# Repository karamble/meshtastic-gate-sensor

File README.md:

# Meshtastic Gate & Door Sensor

Carrier board + firmware that bridges a cheap 433 MHz wireless door sensor onto a private Meshtastic LoRa mesh. A trigger on the door raises an event on the mesh — no WiFi, no cloud, no gateway.

## Architecture

```
KERUI D026 (433 MHz) → RXB6 Receiver → Arduino Nano → UART → Heltec LoRa32 V3 → LoRa mesh
```

The 433 MHz sensor broadcasts a fixed code on every open/close event. An Arduino Nano decodes the code with `rc-switch` on D2 (INT0) and forwards a short text line over SoftwareSerial D3 → voltage divider → Heltec GPIO47. The Heltec runs stock Meshtastic with the serial module in `TEXTMSG` mode at 9600 baud and relays each line into the mesh. A 10 s debounce collapses the KERUI retransmit burst into one mesh event per physical opening.

Firmware emits `Gate: TRIGGERED` on every event and `GATE NODE: Online` every 5 minutes as a heartbeat. KERUI D026 sends the same code on open and close, so `CODE_CLOSED` is disabled by default — one code per event is all you get.

Powered by a Waveshare Solar Power Manager D with 2× 18650 batteries and a 6 V 2 W solar panel. Total draw ≈ 105 mA.

## Carrier PCB v2.3

Custom 75×66 mm 2-layer board with:

- Heltec LoRa32 V3 socket (2×18 pins)
- Arduino Nano socket (2×15 pins, 15.24 mm row spacing)
- RXB6 433 MHz receiver (8-pin SIP, direct solder)
- Logic level divider 2.2k / 3.3k (5V → 3.0V on GPIO47)
- Hardening: 10k DE pull-up, 100nF bypass, 100µF bulk
- GND copper pour on both layers
- 0 DRC violations, 34 netlist self-checks pass

Generated programmatically by `pcb/gate_sensor_pcb_v2.py` and validated with KiCad 10.

## Build

Requires Docker (for KiCad CLI) and PlatformIO.

```bash
make help            # show all targets

# PCB
make drc             # design rule check
make fab             # export Gerbers + drill for JLCPCB

# Firmware
make build           # compile
make upload          # flash the Nano
make monitor         # 115200 USB serial monitor
make learn-sensor    # discover a new 433 MHz sensor's code

# Heltec Meshtastic flash & configure (stock firmware)
./scripts/flash-heltec-meshtastic.sh           # defaults (auto-detect, EU_868)
./scripts/flash-heltec-meshtastic.sh --help
```

The flash script downloads the latest stock Meshtastic release, flashes the Heltec V3, applies the gate-sensor config (GPIO47 RX at 9600 baud, TEXTMSG mode, owner name `GateSensor`/`GATE`, GPS disabled, Bluetooth disabled) and verifies every setting before closing.

## Learning a new sensor

If you're using a different 433 MHz sensor than the KERUI D026, discover its code with:

```bash
make learn-sensor
```

Trigger the sensor a few times and watch for repeating `RF unknown: <decimal>` lines. Copy the decimal into `CODE_OPEN` in `firmware/include/config.h`, re-run `make upload`, and the sensor will fire `Gate: TRIGGERED` on the mesh. See [docs/learn-sensor.md](docs/learn-sensor.md) for details.

## Project Structure

```
├── Makefile                      # build targets (KiCad Docker + PlatformIO)
├── pcb/
│   ├── gate_sensor_pcb_v2.py     # PCB generator script
│   ├── gate_sensor_v2.kicad_pcb  # generated board
│   ├── test_netlist.py           # 34-check PCB self-test
│   ├── generate_assembly.py      # 3D assembly view generator
│   └── logo_silk.json            # raccoon logo silkscreen data
├── firmware/
│   ├── platformio.ini            # PlatformIO config (board=nanoatmega328new)
│   ├── src/main.cpp              # bridge firmware
│   └── include/config.h          # sensor codes, pin defs, timing
├── scripts/
│   └── flash-heltec-meshtastic.sh  # Heltec flash + config
├── docs/
│   ├── schematic.md              # schematic + netlist
│   ├── pcb.md                    # PCB design documentation
│   ├── firmware.md               # firmware documentation
│   ├── assembly.md               # assembly and setup guide
│   ├── learn-sensor.md           # discovering a new 433 MHz sensor code
│   ├── bom.md                    # bill of materials
│   └── ordering.md               # JLCPCB ordering guide
└── pin-outs/                     # component pinout reference images
```

## BOM

~$52 total for one complete sensor node. See [docs/bom.md](docs/bom.md) for the full bill of materials.

## License

ISC — see [LICENSE](LICENSE).

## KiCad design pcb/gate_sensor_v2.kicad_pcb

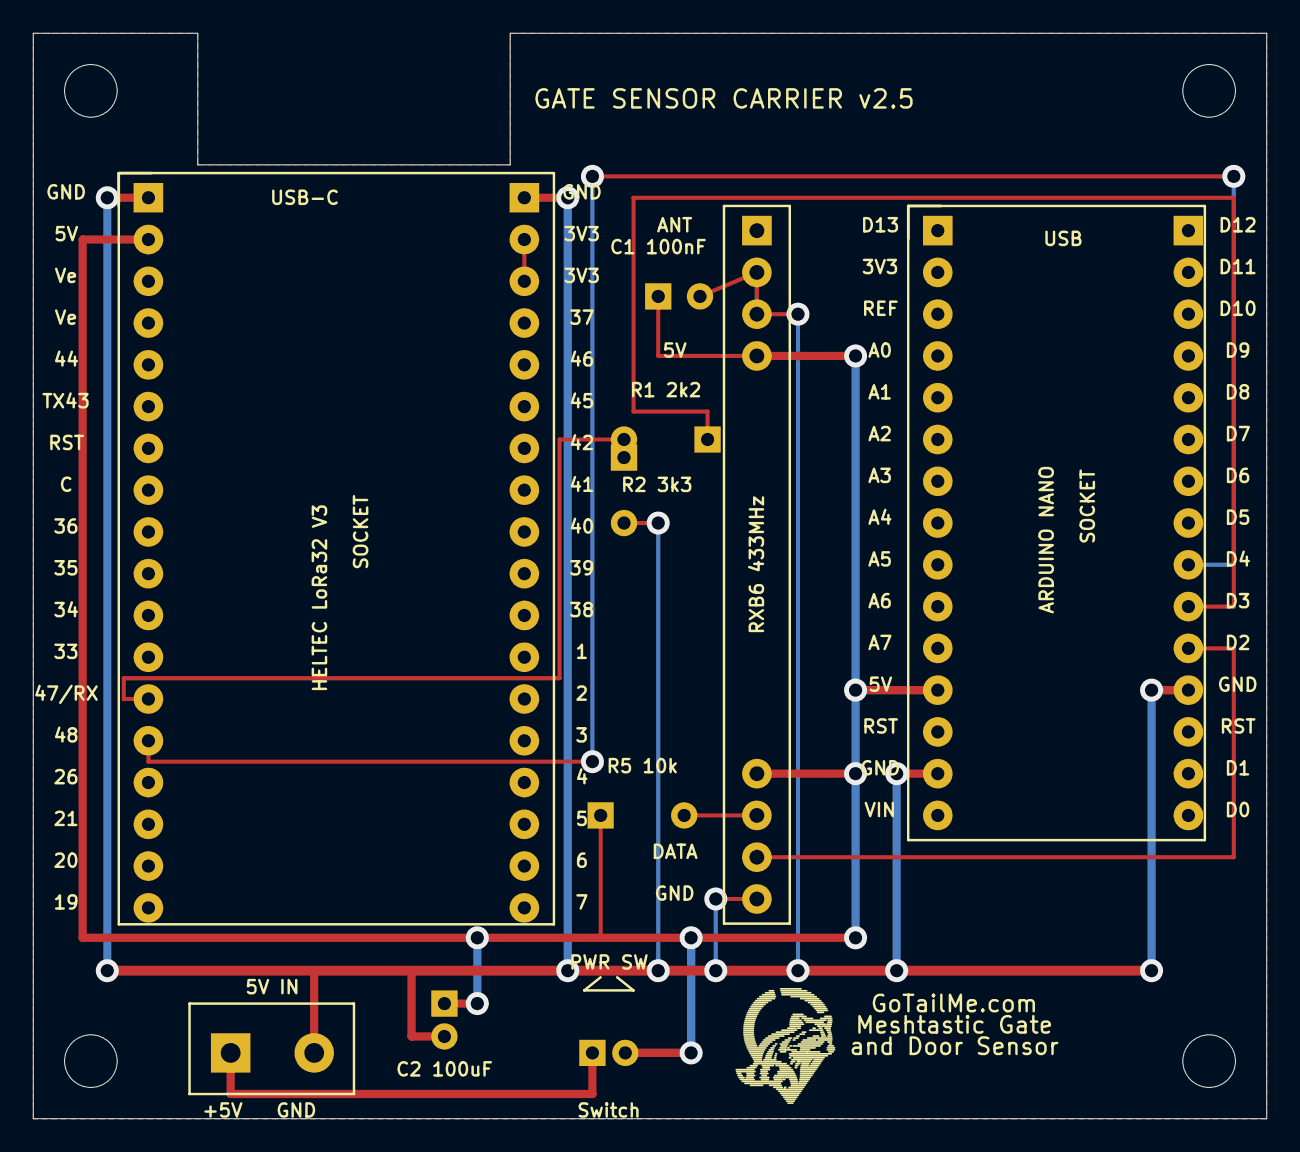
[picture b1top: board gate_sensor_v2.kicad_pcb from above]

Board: 2 copper layers, 75.0 x 66.0 mm, 14 parts (0 on the bottom side), 9 nets.

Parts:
C1: 100nF; C1
C2: 100uF; C2
J2: PWR_IN_ScrewTerm; J2
J4: PWR_SW_JST_PH_2pin; J4
MH: M3_MountHole; MH
MH#2, MH#3, MH#4: M3_MountHole; MH
R1: 2.2k; R1
R2: 3.3k; R2
R5: 10k_PU; R5
U1: Arduino_Nano_Socket; U1
U2: RXB6_433MHz_DirectSolder; U2
U3: Heltec_LoRa32_V3; U3

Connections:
3V3: U3.R2, U3.R3
5V: C1.1, C2.1, J4.2, R5.1, U1.L12, U2.4, U2.5, U3.L2
5V_IN: J2.1, J4.1
D2: U1.R11, U2.7
D3: R1.1, U1.R10
DE: R5.2, U2.6
GND: C1.2, C2.2, J2.2, R2.2, U1.L14, U1.R12, U2.2, U2.3, U2.8, U3.L1, U3.R1
HELTEC_RX: R1.2, R2.1, U3.L13
HELTEC_TX: U1.R9, U3.L14

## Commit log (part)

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2026-04-04 Initial commit — Gate Sensor Carrier PCB v2.2
    Meshtastic gate sensor carrier board (75x66mm, 2-layer) for
    Heltec LoRa32 V3 + Arduino Nano + RXB6 433MHz receiver.
    PCB: KiCad 10, generated by gate_sensor_pcb_v2.py, 0 DRC violations.
    Firmware: PlatformIO skeleton for ATmega328P bridge (RCSwitch + SoftwareSerial).
    Docs: schematic, BOM, assembly guide.
2026-04-04 Fix stale D4/GPIO44 references from pre-review pin changes
    Rename D4_NET→D2_NET and D4_RXB_X→D2_RXB_X to match actual wiring
    (RXB6 DATA connects to Nano D2/INT0, not D4). Fix silkscreen text
    from GPIO44 to GPIO47 for Heltec serial RX pin.
2026-04-04 PCB v2.3: remove battery monitoring, add 3D assembly view
    The Waveshare Solar Power Manager D handles battery internally —
    no BAT pin is accessible for voltage monitoring from the carrier PCB.
    PCB changes:
    - Remove R3, R4 (battery voltage divider) and J3 (battery connector)
    - Simplify V5 bus to straight run (no R4 notch)
    - Move R1/R2 right 2mm, restoring Heltec pins 40-42 to silkscreen
2026-04-05 Fix remaining stale D4 references in docs and comments
    The RF DATA net was renamed from D4 to D2 when the pin changed,
    but five documentation/comment locations still referenced D4.
2026-04-05 Add JLCPCB ordering guide
    Step-by-step guide for ordering PCBs from JLCPCB: Gerber export,
    order form settings, and recommended options for the 2-layer board.
2026-04-05 Fix Arduino Nano left/right pin swap and digital pin order
    The Nano socket had analog/power pins on the RIGHT and digital pins
    on the LEFT — reversed from the real board. Digital pin order was also
    inverted (D1 at USB end instead of D12). Verified against 4 reference
    pinout images.
    - Swap NL/NR arrays: LEFT=analog/power, RIGHT=digital (descending)
    - Re-route D3 (R10→R1) all-F.Cu via top of board
2026-04-05 Fix D0/D1 label order on Nano right column
    CH340 Nano pinout images (3 of 4 references) show D1 above D0 at the
    bottom of the digital pin column. Swap silkscreen labels to match.
    No routing impact — neither pin has a net connected.
2026-04-05 Adjust silkscreen labels: center socket names, add USB label to Nano
    - Move Heltec/Nano/RXB6 socket labels up for better vertical centering
    - Add "USB" label at top of Arduino Nano socket frame
    - Center R1 2k2 label above resistor body
2026-04-05 Add Heltec Meshtastic flash script for gate sensor node
    Automates flash + configure workflow for Heltec V3 as gate sensor:
    - BAUD_9600 (matches Nano SoftwareSerial)
    - serial.rxd=47 (GPIO47, avoids CP2102 conflict)
    - serial.txd=0 (one-way UART, Nano does not receive)
    - Stock Meshtastic firmware (no custom build required)
    - Includes config verification step
2026-04-05 Add PCB netlist verification test (34 checks)
    Validates net pad membership, forbidden connections, firmware pin
    mapping, Nano pin order (L/R swap regression), voltage divider
    correctness, and trace connectivity by parsing the generated KiCad
    PCB file. Run with: make test-netlist
2026-04-05 Update JLCPCB ordering guide with all form options
    Cover every high-spec and advanced option in the order form:
    via plating, min via size, blind slots, UL marking, 4-wire Kelvin
    test, appearance quality, silkscreen technology, package box,
    inspection report, and PCB remark fields.
2026-04-16 Calibrate Nano firmware to KERUI D026 sensor
    - CODE_OPEN=150910 — decimal value learned from a real KERUI D026 via
    rc-switch.
    - CODE_CLOSED disabled: the sensor emits the same code on open and
    close, so no distinct close event is decodable. Emit "TRIGGERED"
    rather than "OPEN" to match that reality.
    - DEBOUNCE_MS raised from 200 to 10000 to collapse the KERUI retransmit
2026-04-16 Fix flash script after end-to-end bench test
    - Release asset naming: Meshtastic 2.7+ dropped the .factory.bin suffix,
    so the factory image is now firmware-heltec-v3-<ver>.bin and there is
    a sibling *-update.bin OTA delta that must NOT be flashed at 0x00.
    Update the glob to match the factory image and exclude the update
    image explicitly.
    - serial.txd=0 silently kills SerialModule RX on ESP32-S3: GPIO0 is the
2026-04-16 Add sensor-learning workflow (docs + make target)
    Replaces the ambiguous "run the RCSwitch ReceiveDemo example" pointer
    in docs/assembly.md with a concrete procedure that reuses the already
    shipped firmware. Every RF hit that doesn't match CODE_OPEN is printed
    on USB serial as "RF unknown: <decimal>" — so the user just flashes
    the production firmware, triggers their new sensor, notes the
    repeating decimal, sets CODE_OPEN, and re-flashes.
2026-04-16 Rewrite README: drop obsolete project reference, reflect current state
    - Drop the old project name from the title; this repo is a standalone
    meshtastic gate sensor.
    - PCB version 2.2 → 2.3 to match the current board and docs.
    - Expand the architecture paragraph to name the real signal chain
    (rc-switch on D2/INT0, SoftwareSerial D3, voltage divider into GPIO47,
    TEXTMSG mode at 9600 baud) and document the current message format
2026-04-16 Add ISC LICENSE file and fix README license reference
2026-04-16 Sync assembly.md Phase 2/3 with current workflow
    Phase 2 now points at make learn-sensor (production firmware prints
    RF unknown: <decimal> on USB serial) instead of the old RCSwitch
    ReceiveDemo sketch. Default CODE_OPEN=150910 for KERUI D026 noted;
    CODE_CLOSED stays at 0 since the sensor emits the same code on
    open and close. Verify step shows Gate: TRIGGERED with the 10 s
    debounce behaviour.
2026-04-16 PCB v2.3: move R5 silkscreen label to F.SilkS
    The R5 reference text was only placed on F.Fab in v2.2, so the
    physical board showed a resistor footprint with no printed label —
    easy to miss during assembly. Flip the label to F.SilkS and center
    it 3 mm above the body, matching the R1 convention. The verbose
    "DE pullup" note stays on F.Fab.
    The label needed to move above the resistor (Y - 3.0) rather than
2026-04-16 Sync remaining docs with current firmware + PCB v2.3
    bom.md
    - Title reflects both cost variants (~$52 with solar, ~$36 bare)
    - Cost summary table added (with / bare / USB-C adapter)
    - Carrier PCB row bumped v2.2 → v2.3
    - R5 marked Optional (DNP): RXB6 DE pin floats high on its own
    with the batches this build has seen, so the pull-up is cheap
2026-04-19 Replace fixed heartbeat with AntiHunter-compatible STATUS frame
    Drop the 5-min "GATE NODE: Online" fixed-string heartbeat and emit a
    STATUS frame instead, on boot and every 30 min. Shape matches the
    AntiHunter STATUS regex (meshtastic-rewrite.parser.ts:10 in CC PRO) so
    the frame parses cleanly in every portal in the ecosystem.
    Adds a trailing Type: field that carries the sensor-class identifier
    ("GATESENSOR" today, extensible to DOOR / MOTION / WINDOW on future
2026-04-19 PCB v2.4: add Heltec GPIO48 -> R6 -> Nano D4 RX path
    Enables bidirectional UART between the Heltec LoRa32 V3 and the Arduino
    Nano. The Nano can now receive Meshtastic serial frames in addition to
    sending RF events on D3.
    R6 (4.7k) sits in series on the new trace as a back-feed limiter: when
    the Heltec is USB-powered alone (e.g. during flashing) and the Nano's
    5V rail is off, GPIO48 driving HIGH would otherwise forward-bias the
2026-04-19 Firmware: CMD handler for STATUS, HB_ON, HB_OFF, HB_INTERVAL
    The Nano can now receive plain-text command frames over SoftwareSerial
    RX (D4, fed by Heltec GPIO48 through R6 from PCB v2.4). This enables
    remote operators (e.g. diginode-cc) to query and reconfigure the
    sensor without reflashing.
    Wire format: @<target> <verb>[:<param>...]\n
    Target is matched case-insensitively against ALL or SENSOR_NAME. Other
2026-04-19 Firmware: REBOOT, HITS_RESET, DEBOUNCE_SET, dynamic code registry
    Adds domain-appropriate CMD verbs on top of the existing STATUS/HB_*
    framework and replaces the single compile-time 433 MHz code with a
    runtime-mutable list of up to 16 codes persisted in EEPROM.
    System:
    REBOOT watchdog-triggered soft reset; ACK-before-
    reset so the operator sees REBOOT_ACK:OK
2026-04-19 PCB v2.4: silkscreen polish — logo 1.2x, text shift, layout tweaks
    - Scaled the bottom-right raccoon logo by 1.2x anchored at its
    top-left so the top edge stays in place and the previously empty
    space below the logo is filled. New logo bottom Y=65.1 still clears
    the 0.5 mm board-edge rule at Y=66.
    - Shifted the "GoTailMe.com / Meshtastic Gate / and Door Sensor" text
    block from X=54 to X=56 so the larger logo has breathing room.
2026-04-19 PCB v2.5 cleanup: docs, netlist test, config comment, Makefile
    Sweep up remaining R6 references after the v2.5 direct-trace rework:
    - docs/schematic.md: remove R6 from block diagram and hardening
    components; rewrite the D4 net line as HELTEC_TX direct to U1-R9;
    fix a pre-existing typo where RXB6 pin 7 was listed on net D4
    instead of D2.
    - docs/firmware.md, docs/bom.md: drop R6 from library notes, pin
2026-04-19 Firmware: strip Meshtastic TEXTMSG <sender>: prefix in processCmdLine
    The Heltec's Meshtastic Serial module prepends the sender's short-name
    (e.g. "1e44: @GATE HB_OFF") to every received broadcast in TEXTMSG
    mode, so the first char is a hex digit, not '@'. The old parser
    bailed when line[0] != '@' and silently dropped every inbound command.
    Search for '@' with strchr and advance past whatever precedes it.
    Pairs with PCB v2.5's direct GPIO48 -> D4 trace to close the loop
2026-04-19 Firmware: 8s boot delay before first STATUS to let Heltec come up
    Nano boots in ~50ms; Meshtastic on the Heltec needs several seconds to
    bring up its Serial module. The boot STATUS was being fired into a dead
    UART and dropped.
2026-04-20 Makefile: auto-detect Nano FTDI port for upload/monitor
    Resolves the Nano via the persistent /dev/serial/by-id/usb-FTDI_FT232R_*
    symlink so pio doesn't pick a co-plugged Heltec's CP2102 (which yields
    "avrdude: not in sync" with random Meshtastic log bytes). Errors out if
    zero or multiple FTDI devices are present.
2026-04-20 docs/firmware: call out DM dead end, broadcasts only
    Adds a callout in the CMD Protocol section explaining why direct
    messages can't reach the Nano (Meshtastic SerialModule TEXTMSG mode
    stopped forwarding DMs to UART in fw 2.5) and how DigiNode CC's
    chat-send rewrites DMs as @<ShortName> broadcasts on the user's behalf.
2026-04-20 3dcase: add v1 housing Fusion 360 source and STL
2026-04-20 Firmware: named codes, TRIGGERED format, per-code debounce
    - EEPROM-backed parallel name table (16 slots × 16 bytes) with
    CODE_ADD:<code>[:<name>] / CODE_REMOVE / CODE_LIST / CODE_CLEAR.
    - New frame format "Gate: TRIGGERED:<code> <name>" (name="unnamed" when
    absent), replacing the old EVENT:<code>.
    - Unknown codes ≥ UNKNOWN_MIN_CODE broadcast with name "unknown"; short
    bursts stay on USB debug only.
2026-05-02 Heltec flash: add --standalone retail mode (public PSK + BLE on)
    The default flow flashes a private PSK from .env and disables Bluetooth
    — right for developer/private-mesh deployments but wrong for retail. A
    unit going to a first-time buyer should join the public LongFast channel
    out of the box (so any stock Meshtastic node sees it without setup) and
    keep BLE enabled so the buyer can pair the Meshtastic mobile app and
    generate their own private PSK from there.
